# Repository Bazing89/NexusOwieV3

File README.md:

# NexusOwie

NexusOwie combines the Owie firmware with the custom Owie12FV3 ESP-12F interface board.

## PCB files

- `Owie12FV3/` contains the KiCad schematic, PCB layout, project configuration, render, BOM, component positions, netlist, and fabrication ZIP.
- `Owie12FV3 Panel 2x3/` contains the KiCad 2×3 production panel and panel fabrication files.

Open `Owie12FV3/Owie12FV3.kicad_pro` in KiCad to edit the board.

## Firmware

The firmware is a PlatformIO project. Build it with:

```sh
pio run
```

## Safety

This is an unaffiliated hobby project provided without warranty. Working on battery systems can cause equipment damage, fire, serious injury, or death. Verify the design and fabrication outputs independently before manufacturing or installation.

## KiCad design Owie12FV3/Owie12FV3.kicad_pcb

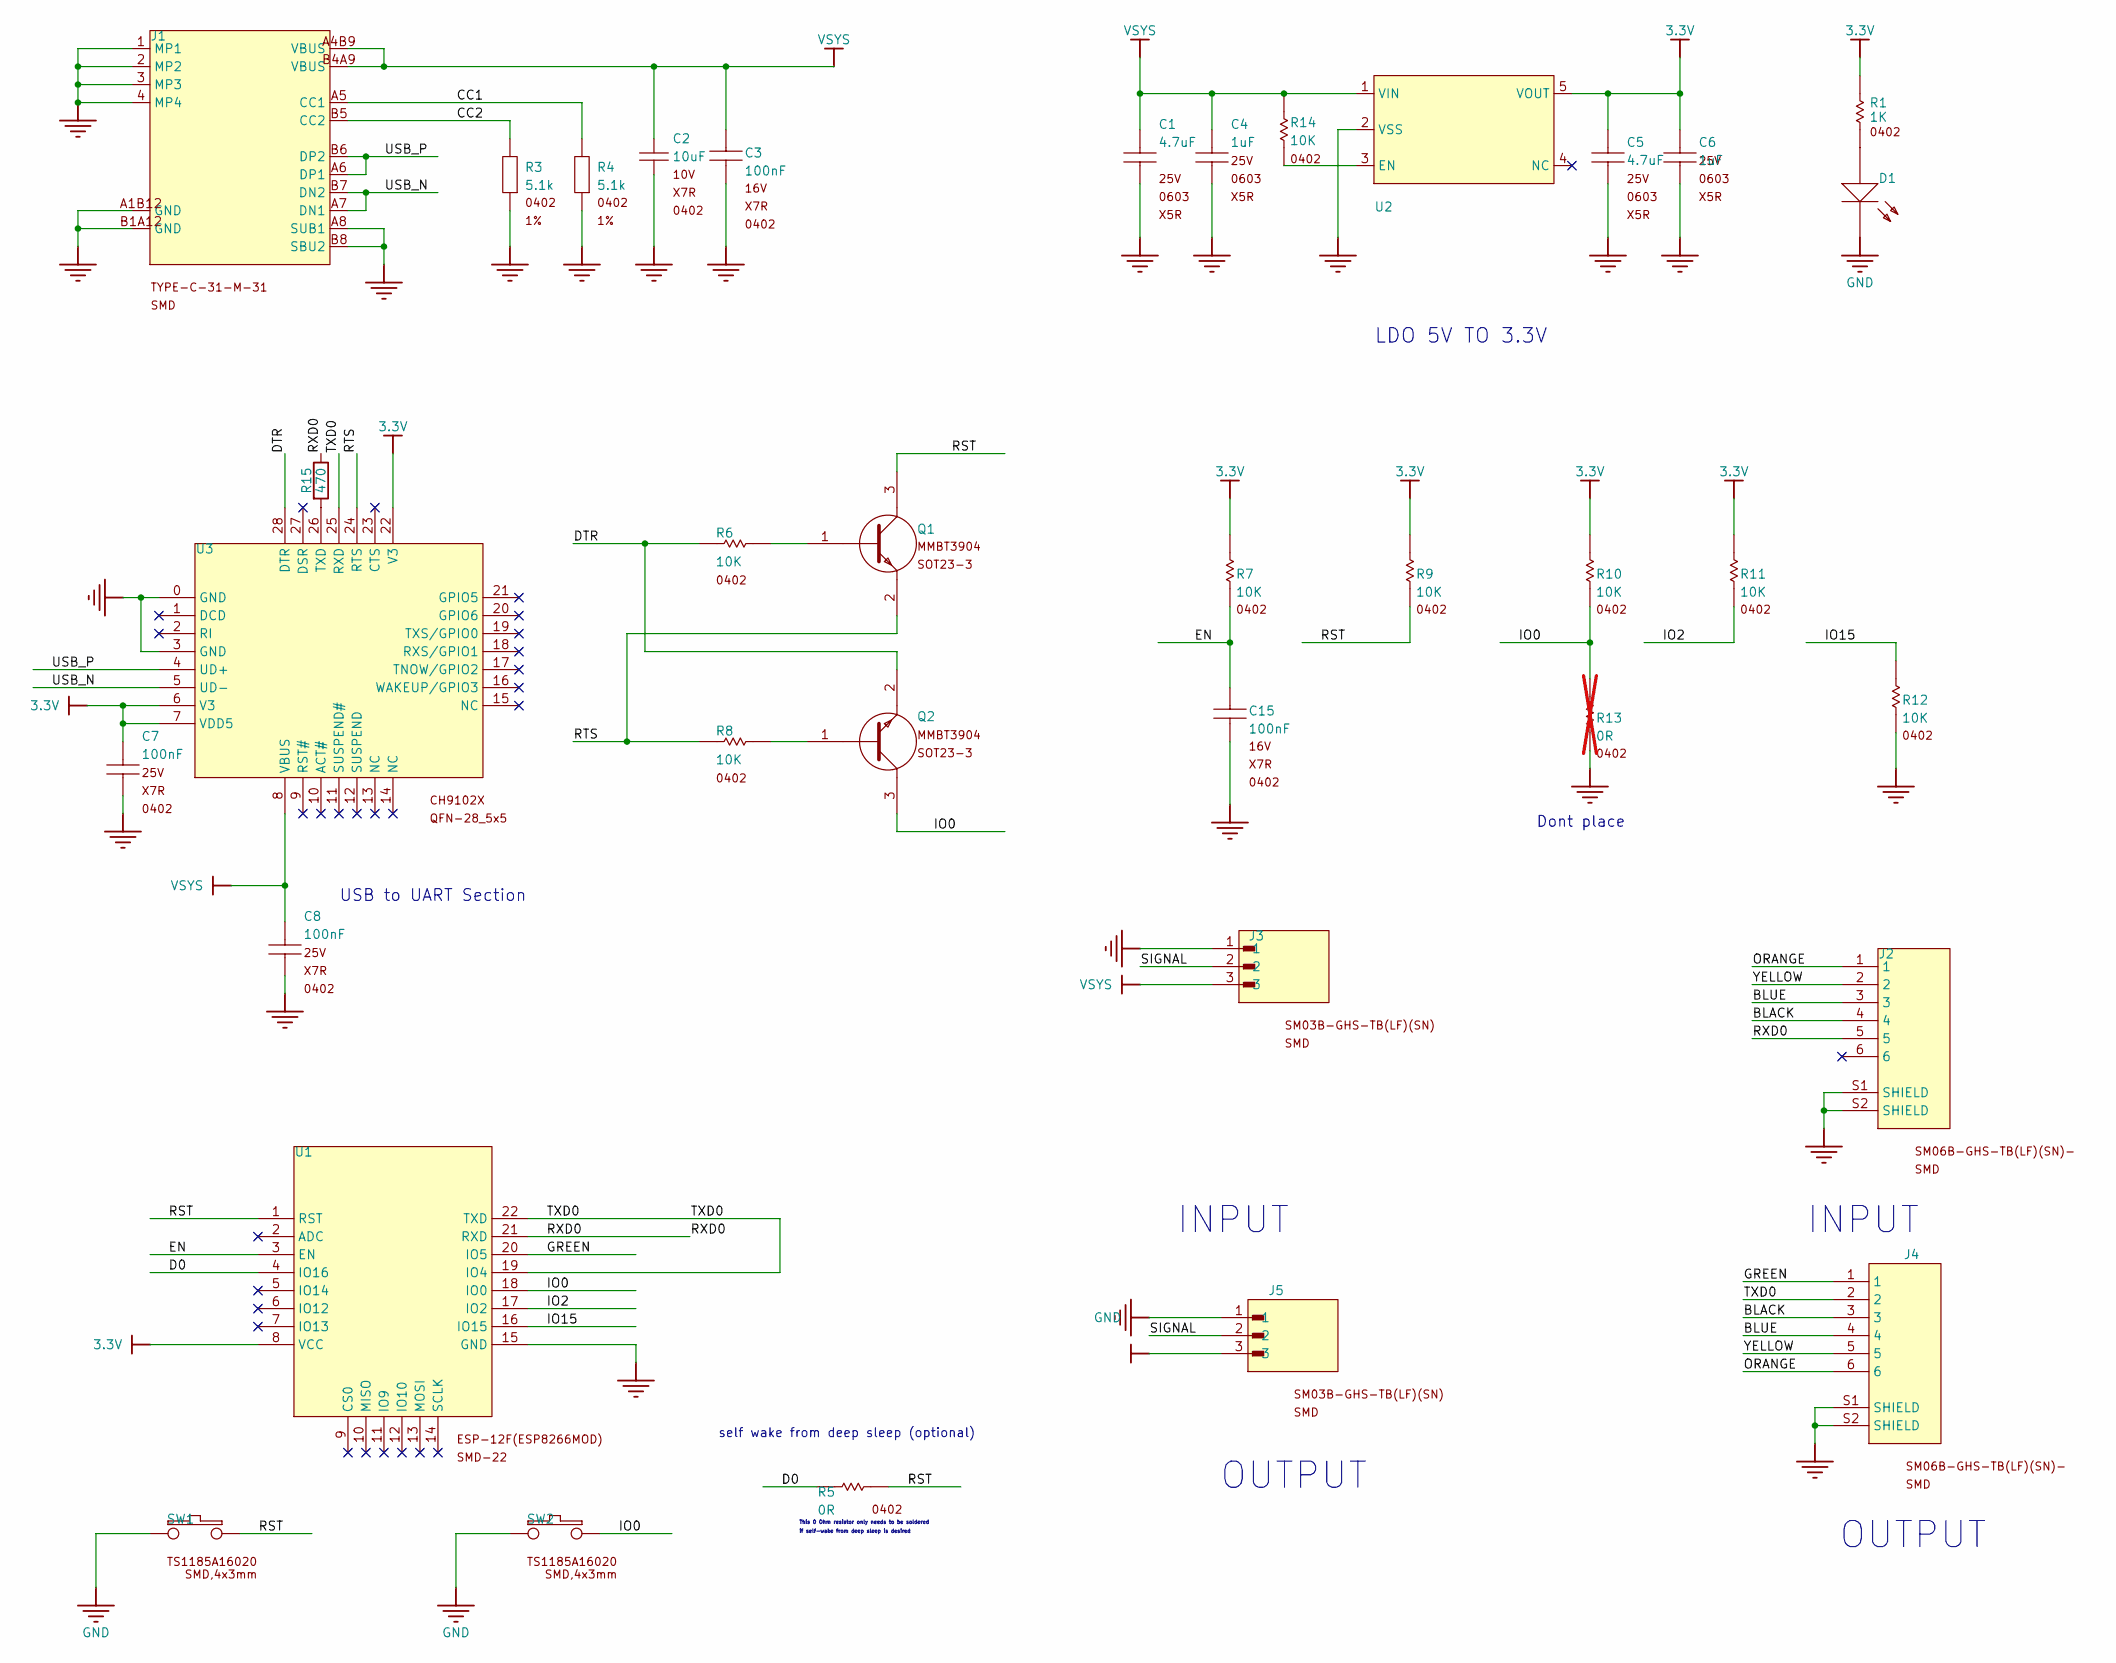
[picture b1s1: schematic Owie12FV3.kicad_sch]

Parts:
C1, C5: 4.7uF; CAPC0603; VOLTAGE 25V; MANUFACTURER PART NUMBER CL10A475KO8NNNC; LCSC Part # C19666
C2: 10uF; CAPC0402; VOLTAGE 10V; MANUFACTURER PART NUMBER CL05A106MQ5NUNC; LCSC Part # C15525
C3, C15: 100nF; CAPC0402; VOLTAGE 16V; MANUFACTURER PART NUMBER CL05B104KO5NNNC; LCSC Part # C1525
C4, C6: 1uF; CAPC0603; VOLTAGE 25V; MANUFACTURER PART NUMBER CL10A105KB8NNNC; LCSC Part # C15849
C7, C8: 100nF; CAPC0402; VOLTAGE 25V; MANUFACTURER PART NUMBER CL05B104KO5NNNC; LCSC Part # C1525
D1: NO; LED_0603; MANUFACTURER PART NUMBER KT-0603W; LCSC Part # C2290
J1: USB-TYPE-C-V000731; TYPE-C16PIN; MANUFACTURER PART NUMBER USB-TYPE-C-009; LCSC Part # C2927029
J2, J4: SM06B-GHS-TB(LF)(SN); JST_SM06B-GHS-TB(LF)(SN); MANUFACTURER PART NUMBER HCZZ0014-6; LCSC Part # C7433487
J3, J5: SM03B-GHS-TB(LF)(SN); JST_SM03B-GHS-TB(LF)(SN); MANUFACTURER PART NUMBER HCZZ0014-3; LCSC Part # C7433484
Q1, Q2: NO; SOT23-3; MANUFACTURER PART NUMBER MMBT3904(RANGE:100-300); LCSC Part # C20526
R1: 1K; RESC0402; MANUFACTURER PART NUMBER 0402WGF1001TCE; LCSC Part # C11702
R3, R4: 5.1k; RESC0402; TOLERANCE 1%; MANUFACTURER PART NUMBER 0402WGF5101TCE; LCSC Part # C25905
R5: 0R; RESC0402; MANUFACTURER PART NUMBER 0402WGF0000TCE; LCSC Part # C17168
R6, R7, R8, R9, R10, R11, R12, R14: 10K; RESC0402; MANUFACTURER PART NUMBER 0402WGF1002TCE; LCSC Part # C25744
R13: 0R; RESC0402; MANUFACTURER PART NUMBER 0402WGF0000TCE; LCSC Part # C17168; not fitted
R15: 470; R_0402_1005Metric; MANUFACTURER PART NUMBER 0402WGF4700TCE; LCSC Part # C25117
SW1, SW2: NO; SW_Micro_push; MANUFACTURER PART NUMBER TS1185A16020; LCSC Part # C22435660
U1: ESP8266; WIFIM-SMD_ESP-12F-ESP8266MOD; MANUFACTURER PART NUMBER ESP-12F; LCSC Part # C19949064
U2: ME6211C33M5G-N; SOT23-5; MANUFACTURER PART NUMBER ME6211C33M5G-N; LCSC Part # C82942
U3: NO; QFN28_5X5; MANUFACTURER PART NUMBER CH9102X; LCSC Part # C5187522

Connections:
3.3V: C5.2, C6.2, C7.2, R1.1, R7.2, R9.2, R10.2, R11.2, U1.8 (VCC), U2.5 (VOUT), U3.6 (V3), U3.7 (VDD5), U3.22 (V3)
/BLACK: J2.4, J4.3
/BLUE: J2.3, J4.4
/CC1: J1.A5 (CC1), R4.2
/CC2: J1.B5 (CC2), R3.2
/D0: R5.1, U1.4 (IO16)
/DTR: Q2.2 (E), R6.2, U3.28 (DTR)
/EN: C15.1, R7.1, U1.3 (EN)
/GREEN: J4.1, U1.20 (IO5)
/IO0: Q2.3 (C), R10.1, R13.2, SW2.1, U1.18 (IO0)
/IO2: R11.1, U1.17 (IO2)
/IO15: R12.2, U1.16 (IO15)
/ORANGE: J2.1, J4.6
/RST: Q1.3 (C), R5.2, R9.1, SW1.1, U1.1 (RST)
/RTS: Q1.2 (E), R8.2, U3.24 (RTS)
/RXD0: J2.5, R15.1, U1.21 (RXD)
/SIGNAL: J3.2, J5.2
/TXD0: J4.2, U1.19 (IO4), U1.22 (TXD), U3.25 (RXD)
/USB_N: J1.A7 (DN1), J1.B7 (DN2), U3.5 (UD-)
/USB_P: J1.A6 (DP1), J1.B6 (DP2), U3.4 (UD+)
/YELLOW: J2.2, J4.5
GND: C1.1, C2.2, C3.2, C4.1, C5.1, C6.1, C7.1, C8.1, C15.2, D1.K, J1.1 (MP1), J1.2 (MP2), J1.3 (MP3), J1.4 (MP4), J1.A1B12 (GND), J1.A8 (SUB1), J1.B1A12 (GND), J1.B8 (SBU2), J2.S1 (SHIELD), J2.S2 (SHIELD), J3.1, J4.S1 (SHIELD), J4.S2 (SHIELD), J5.1, R3.1, R4.1, R12.1, R13.1, SW1.2, SW2.2, U1.15 (GND), U2.2 (VSS), U3.0 (GND), U3.3 (GND)
unnamed: D1.A, R1.2
unnamed: Q1.1 (B), R6.1
unnamed: Q2.1 (B), R8.1
unnamed: R14.2, U2.3 (EN)
unnamed: R15.2, U3.26 (TXD)
VSYS: C1.2, C2.1, C3.1, C4.2, C8.2, J1.A4B9 (VBUS), J1.B4A9 (VBUS), J3.3, J5.3, R14.1, U2.1 (VIN), U3.8 (VBUS)

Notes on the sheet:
This 0 Ohm resistor only needs to be soldered
USB to UART Section
INPUT
if self-wake from deep sleep is desired
OUTPUT
LDO 5V TO 3.3V
self wake from deep sleep (optional)
Dont place

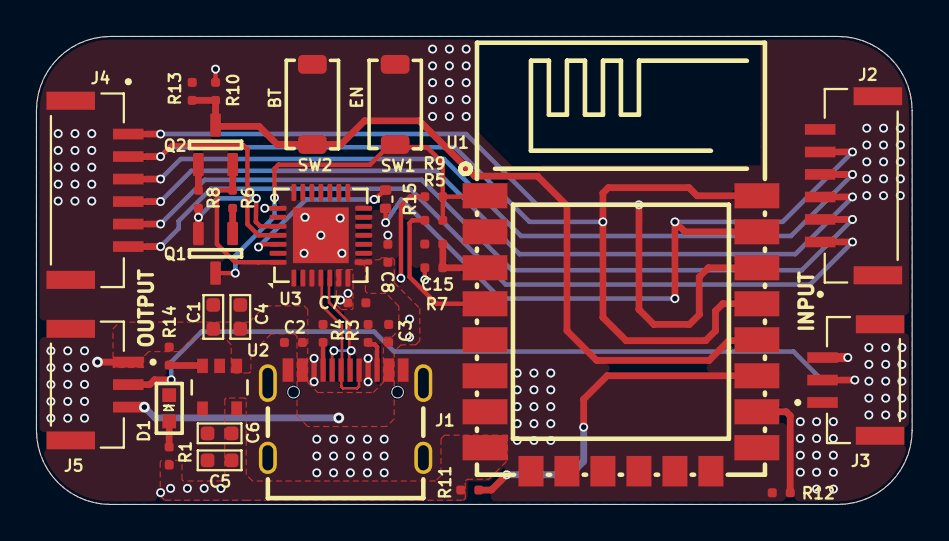
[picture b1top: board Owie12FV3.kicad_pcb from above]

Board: 2 copper layers, 48.6 x 26.0 mm, 36 parts (0 on the bottom side), 28 nets.

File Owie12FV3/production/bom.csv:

Designator,Footprint,Quantity,Value,LCSC Part #
"C1, C5",CAPC0603,2,4.7uF,C19666
"C15, C3, C7, C8",CAPC0402,4,100nF,C1525
C2,CAPC0402,1,10uF,C15525
"C4, C6",CAPC0603,2,1uF,C15849
D1,LED_0603,1,NO,C2290
J1,TYPE-C16PIN,1,TYPE-C16PIN,C393939
"J2, J4",JST_SM06B-GHS-TB(LF)(SN),2,SM06B-GHS-TB(LF)(SN),C7433487
"J3, J5",JST_SM03B-GHS-TB(LF)(SN),2,SM03B-GHS-TB(LF)(SN),C7433484
"Q1, Q2",SOT23-3,2,NO,C20526
R1,RESC0402,1,1K,C11702
"R10, R11, R12, R14, R6, R7, R8, R9",RESC0402,8,10K,C25744
R15,0402,1,470,C25117
"R3, R4",RESC0402,2,5.1k,C25905
R5,RESC0402,1,0R,C17168
"SW1, SW2",SW_Micro_push,2,NO,C22435660
U1,WIFIM-SMD_ESP-12F-ESP8266MOD,1,ESP8266,C19949064
U2,SOT23-5,1,ME6211C33M5G-N,C82942
U3,QFN28_5X5,1,NO,C5187522

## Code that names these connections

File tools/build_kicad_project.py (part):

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sch += comp("owie_custom:USB_C_16", "J1", "TYPE-C-31-M-31", 1900, 1800, "")
for yy in (1050, 1300, 1550, 1800, 2200, 2500):
    sch += label("GND", 1200, yy)
sch += label("VSYS", 2600, 1000); sch += label("VSYS", 2600, 1200)
sch += label("CC1", 2600, 1400); sch += label("CC2", 2600, 1600)
sch += label("USB_P", 2600, 1800); sch += label("USB_P", 2600, 2000)
sch += label("USB_N", 2600, 2200); sch += label("USB_N", 2600, 2400)
sch += label("GND", 2600, 2600); sch += label("GND", 2600, 2750)

for ref, net, x in (("R3", "CC1", 3300), ("R4", "CC2", 3900)):
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    sch += wire(x, 1800, x, 1900); sch += label("GND", x, 1900)
for ref, val, x in (("C2", "10uF 10V X7R 0402", 4600), ("C3", "100nF 16V X7R 0402", 5200)):
    sch += comp("owie_custom:C", ref, val, x, 1500, "Capacitor_SMD:C_0402_1005Metric")
    sch += wire(x, 1400, x, 1300); sch += label("VSYS", x, 1300)
    sch += wire(x, 1600, x, 1700); sch += label("GND", x, 1700)

# LDO and LED
sch += note("LDO 5V TO 3.3V", 6500, 650, 100)
sch += comp("owie_custom:LDO5", "U2", "LDO (value not shown in PDF)", 7600, 1500, "Package_TO_SOT_SMD:SOT-23-5")
sch += label("VSYS", 7100, 1350); sch += label("GND", 7100, 1500); sch += label("EN_LDO", 7100, 1650)
sch += label("3.3V", 8100, 1350); sch += nocon(8100, 1650)
for ref, val, net, x, fp in (
    ("C1", "4.7uF 25V X5R 0603", "VSYS", 6100, "Capacitor_SMD:C_0603_1608Metric"),
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    sch += wire(x, 1400, x, 1300); sch += label(net, x, 1300)
    sch += wire(x, 1600, x, 1700); sch += label("GND", x, 1700)
sch += comp("owie_custom:R", "R14", "10K 0402", 7000, 2100, "Resistor_SMD:R_0402_1005Metric")
sch += wire(7000, 2000, 7000, 1900); sch += label("VSYS", 7000, 1900)
sch += wire(7000, 2200, 7000, 2300); sch += label("EN_LDO", 7000, 2300)
sch += comp("owie_custom:R", "R1", "1K 0402", 10500, 1300, "Resistor_SMD:R_0402_1005Metric")
sch += wire(10500, 1200, 10500, 1100); sch += label("3.3V", 10500, 1100)
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    if net: sch += label(net, 1900, yy)
    else: sch += nocon(1900, yy)
# bottom pins 8..14
sch += label("VSYS", 2100, 5800)
for xx in (2300,2500,2700,3100,3300): sch += nocon(xx, 5800)
sch += nocon(2900, 5800)  # pin 12 SUSPEND is NC in source
# right pins 15..21
for yy in (5400,5200,5000,4800,4600,4400,4200): sch += nocon(3500, yy)
# top 22..28
sch += label("3.3V", 2100, 3600); sch += nocon(2300, 3600)
sch += label("RTS", 2500, 3600); sch += label("RXD0", 2700, 3600); sch += label("TXD0", 2900, 3600)
sch += nocon(3100, 3600); sch += label("DTR", 3300, 3600)
sch += comp("owie_custom:C", "C7", "100nF 25V X7R 0402", 1500, 5200, "Capacitor_SMD:C_0402_1005Metric")
sch += wire(1500,5100,1500,5000); sch += label("3.3V",1500,5000); sch += wire(1500,5300,1500,5400); sch += label("GND",1500,5400)
sch += comp("owie_custom:C", "C8", "100nF 25V X7R 0402", 1500, 5800, "Capacitor_SMD:C_0402_1005Metric")
sch += wire(1500,5700,1500,5600); sch += label("VSYS",1500,5600); sch += wire(1500,5900,1500,6000); sch += label("GND",1500,6000)

# Auto-programming transistor network
sch += note("AUTO-PROGRAM RESET / BOOT", 4300, 3300, 90)
sch += comp("owie_custom:R", "R6", "10K 0402", 4700, 4100, "Resistor_SMD:R_0402_1005Metric", (0,-1,-1,0))
sch += wire(4600,4100,4400,4100); sch += label("DTR",4400,4100)
sch += comp("owie_custom:NPN_SOT23", "Q1", "MMBT3904 SOT23-3", 5400, 4100, "Package_TO_SOT_SMD:SOT-23")
sch += wire(4800,4100,5200,4100); sch += label("RTS",5500,4300); sch += label("RST",5500,3900)
sch += comp("owie_custom:R", "R8", "10K 0402", 4700, 5000, "Resistor_SMD:R_0402_1005Metric", (0,-1,-1,0))
sch += wire(4600,5000,4400,5000); sch += label("RTS",4400,5000)
sch += comp("owie_custom:NPN_SOT23", "Q2", "MMBT3904 SOT23-3", 5400, 5000, "Package_TO_SOT_SMD:SOT-23")
sch += wire(4800,5000,5200,5000); sch += label("DTR",5500,5200); sch += label("IO0",5500,4800)

# Boot straps and pullups
sch += note("BOOT STRAPS", 6800, 3300, 90)
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# Input/output connectors
sch += note("INPUT", 9000, 6500, 110)
sch += comp("owie_custom:CONN3", "J3", "SM03B-GHS-TB(LF)(SN) SMD", 9200, 7200, "Connector_JST:JST_GH_SM03B-GHS-TB_1x03-1MP_P1.25mm_Horizontal")
for net, yy in (("GND",7080),("SIGNAL",7200),("VSYS",7320)): sch += label(net,8850,yy)
sch += comp("owie_custom:CONN6_SH", "J2", "SM06B-GHS-TB(LF)(SN) SMD", 12400, 7200, "Connector_JST:JST_GH_SM06B-GHS-TB_1x06-1MP_P1.25mm_Horizontal")
for net, yy in (("ORANGE",6900),("YELLOW",7020),("BLUE",7140),("BLACK",7260),("WHITE_IN",7380)):
    sch += label(net,12050,yy)
sch += nocon(12050,7500); sch += label("GND",12750,7380); sch += label("GND",12750,7500)
sch += note("OUTPUT", 9000, 8600, 110)
sch += comp("owie_custom:CONN3", "J5", "SM03B-GHS-TB(LF)(SN) SMD", 9200, 9300, "Connector_JST:JST_GH_SM03B-GHS-TB_1x03-1MP_P1.25mm_Horizontal")
for net, yy in (("VSYS",9180),("SIGNAL",9300),("GND",9420)): sch += label(net,8850,yy)
sch += comp("owie_custom:CONN6_SH", "J4", "SM06B-GHS-TB(LF)(SN) SMD", 12400, 9300, "Connector_JST:JST_GH_SM06B-GHS-TB_1x06-1MP_P1.25mm_Horizontal")
for net, yy in (("GREEN",9000),("WHITE_OUT",9120),("BLACK",9240),("BLUE",9360),("YELLOW",9480),("ORANGE",9600)):
    sch += label(net,12050,yy)
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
